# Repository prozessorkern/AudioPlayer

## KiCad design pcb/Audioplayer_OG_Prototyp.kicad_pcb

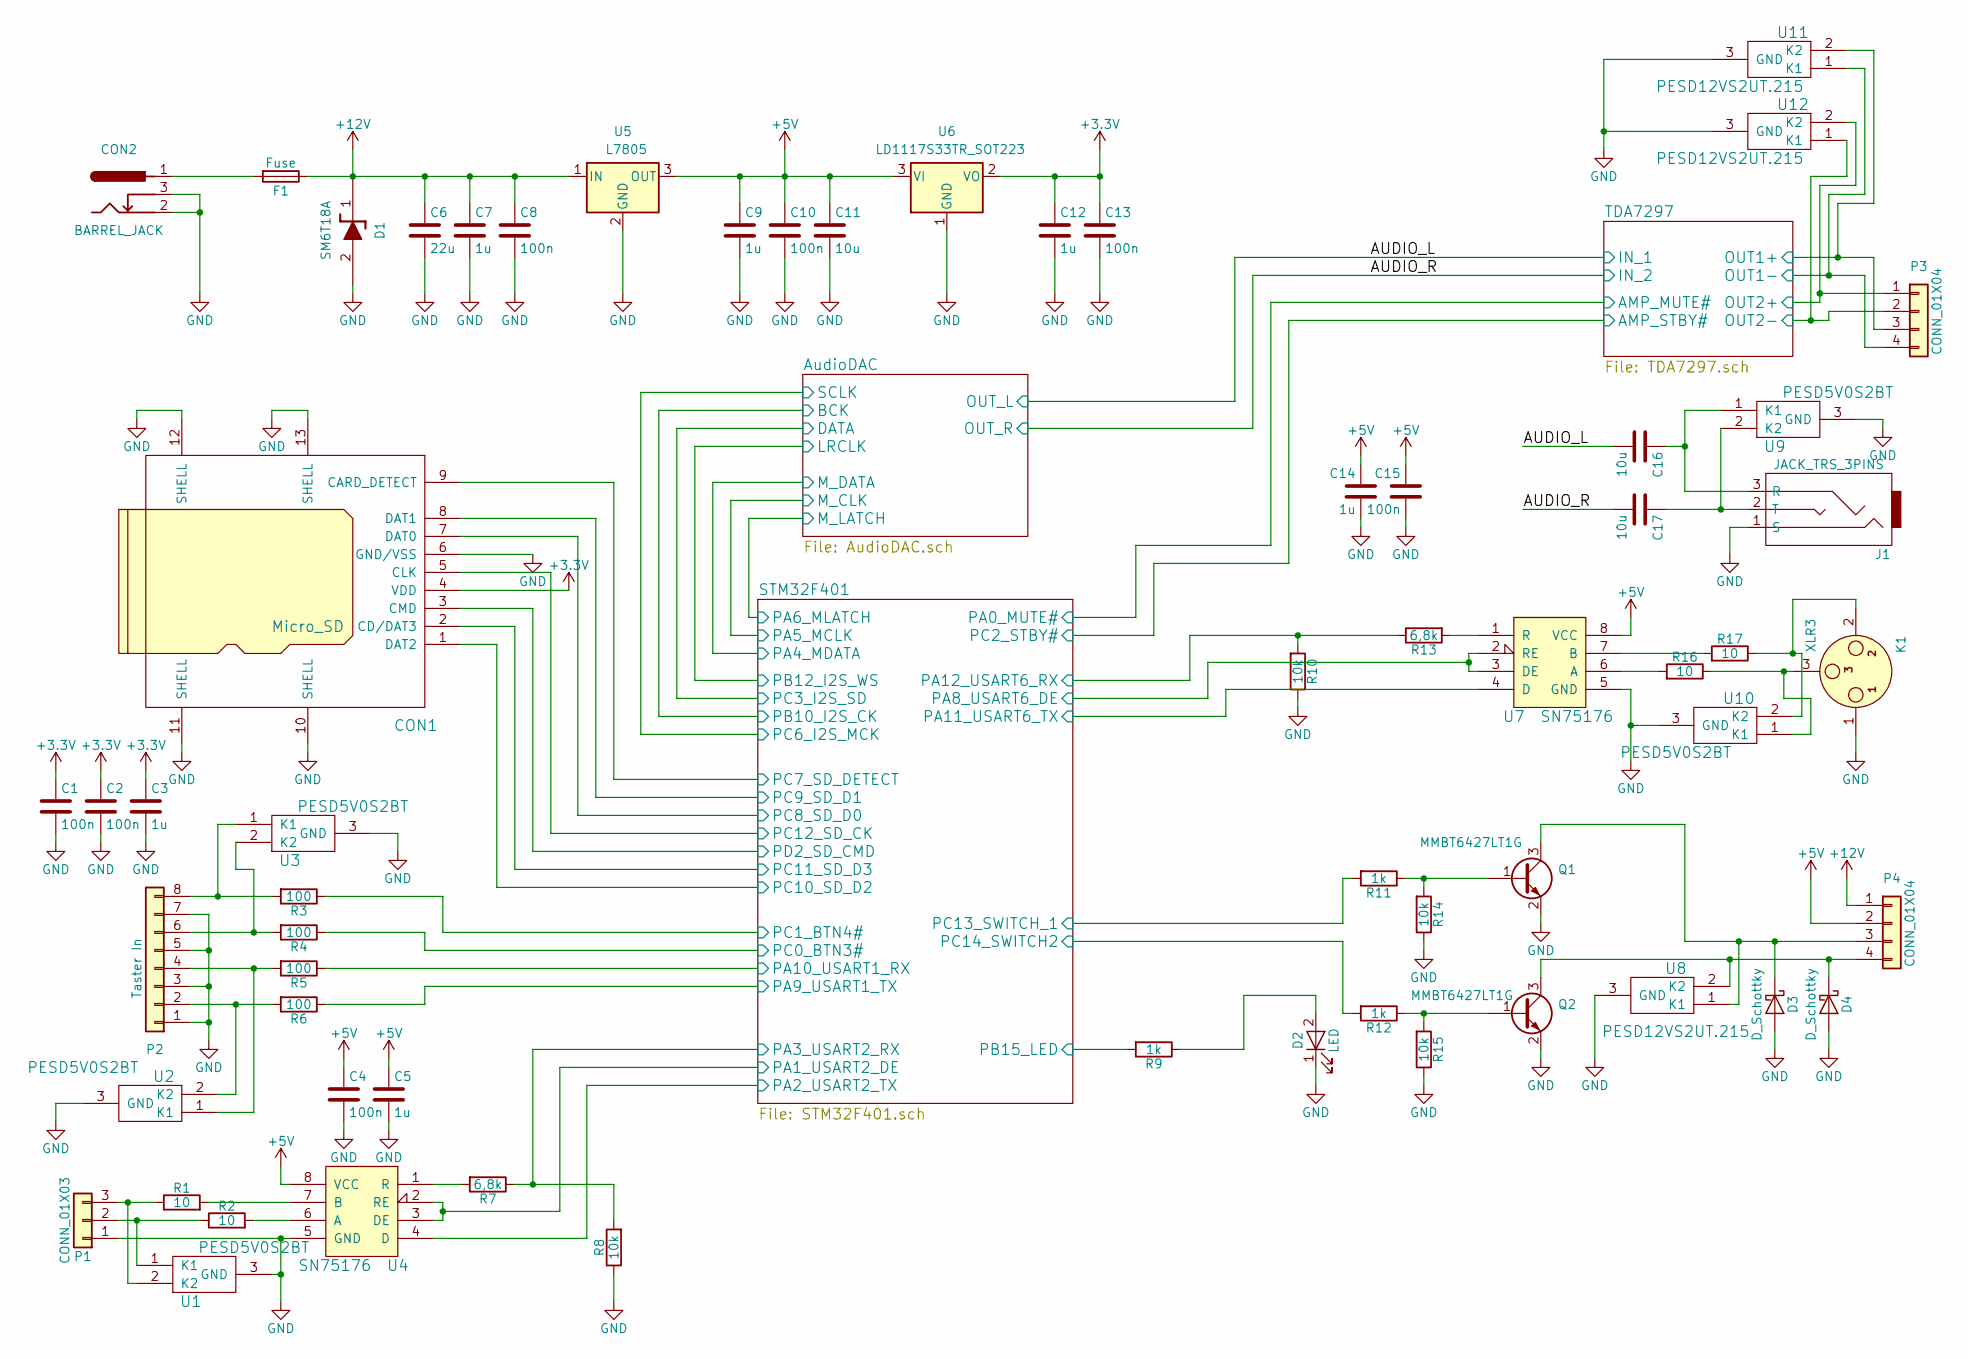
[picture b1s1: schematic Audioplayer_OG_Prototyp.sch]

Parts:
C1, C2, C4, C10, C13, C15: 100n; C_0603_HandSoldering
C3, C5, C9, C12, C14: 1u; C_0603_HandSoldering
C6: 22u; C_1210_HandSoldering
C7: 1u; C_0805_HandSoldering
C8: 100n; C_0805_HandSoldering
C11, C16, C17: 10u; C_0805_HandSoldering
CON1: Micro_SD
CON2: BARREL_JACK; BARREL_JACK_CLIFF
D1: SM6T18A; D_SMB_Handsoldering
D2: LED; LED_D3.0mm
D3, D4: D_Schottky; D_MELF_Handsoldering
F1: Fuse; Fuseholder5x20_ProFUSE
J1: JACK_TRS_3PINS; LUM_1503-07_Klinke
K1: XLR3; NC3FAH1_XLR_F
P1: CONN_01X03; 3PIN_5,00
P2: Taster In; 8PIN_3,5
P3, P4: CONN_01X04; 4PIN_5,00
Q1, Q2: MMBT6427LT1G; SOT-23_Handsoldering
R1, R2, R16, R17: 10; R_0603_HandSoldering
R3, R4, R5, R6: 100; R_0603_HandSoldering
R7, R13: 6,8k; R_0603_HandSoldering
R8, R10, R14, R15: 10k; R_0603_HandSoldering
R9, R11, R12: 1k; R_0603_HandSoldering
U1, U2, U3, U9, U10: PESD5V0S2BT; SOT-23_Handsoldering
U4, U7: SN75176; SO-8
U5: L7805; TO-263-2
U6: LD1117S33TR_SOT223; SOT-223-3_TabPin2
U8, U11, U12: PESD12VS2UT.215; SOT-23_Handsoldering

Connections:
+5V: C4.1, C5.1, C9.1, C10.1, C11.1, C14.1, C15.1, P4.2, U4.8 (VCC), U5.3 (OUT), U6.3 (VI), U7.8 (VCC); also elsewhere on the board
+12V: C6.1, C7.1, C8.1, D1.1, F1.1, P4.1, U5.1 (IN); also elsewhere on the board
/AUDIO_L: C16.2; also elsewhere on the board
/AUDIO_R: C17.2; also elsewhere on the board
/STM32F401/PA1_USART2_DE: U4.2 (RE), U4.3 (DE); also elsewhere on the board
/STM32F401/PA2_USART2_TX: U4.4 (D); also elsewhere on the board
/STM32F401/PA3_USART2_RX: R7.1, R8.2; also elsewhere on the board
/STM32F401/PA8_USART6_DE: U7.2 (RE), U7.3 (DE); also elsewhere on the board
/STM32F401/PA9_USART1_TX: R6.1; also elsewhere on the board
/STM32F401/PA10_USART1_RX: R5.1; also elsewhere on the board
/STM32F401/PA11_USART6_TX: U7.4 (D); also elsewhere on the board
/STM32F401/PA12_USART6_RX: R10.2, R13.1; also elsewhere on the board
/STM32F401/PB15_LED: R9.2; also elsewhere on the board
/STM32F401/PC0_BTN3#: R4.1; also elsewhere on the board
/STM32F401/PC1_BTN4#: R3.1; also elsewhere on the board
/STM32F401/PC7_SD_DETECT: CON1.9 (CARD_DETECT); also elsewhere on the board
/STM32F401/PC8_SD_D0: CON1.7 (DAT0); also elsewhere on the board
/STM32F401/PC9_SD_D1: CON1.8 (DAT1); also elsewhere on the board
/STM32F401/PC10_SD_D2: CON1.1 (DAT2); also elsewhere on the board
/STM32F401/PC11_SD_D3: CON1.2 (CD/DAT3); also elsewhere on the board
/STM32F401/PC12_SD_CK: CON1.5 (CLK); also elsewhere on the board
/STM32F401/PC13_SWITCH_1: R11.2; also elsewhere on the board
/STM32F401/PC14_SWITCH2: R12.2; also elsewhere on the board
/STM32F401/PD2_SD_CMD: CON1.3 (CMD); also elsewhere on the board
/TDA7297/OUT1+: P3.3, U11.2 (K2); also elsewhere on the board
/TDA7297/OUT1-: P3.4, U11.1 (K1); also elsewhere on the board
/TDA7297/OUT2+: P3.1, U12.2 (K2); also elsewhere on the board
/TDA7297/OUT2-: P3.2, U12.1 (K1); also elsewhere on the board
GND: C1.2, C2.2, C3.2, C4.2, C5.2, C6.2, C7.2, C8.2, C9.2, C10.2, C11.2, C12.2, C13.2, C14.2, C15.2, CON1.6 (GND/VSS), CON1.10 (SHELL), CON1.11 (SHELL), CON1.12 (SHELL), CON1.13 (SHELL), CON2.2, CON2.3, D1.2, D2.1 (K), D3.2 (A), D4.2 (A), J1.1 (S), K1.1, P1.1, P2.1, P2.3, P2.5, P2.7, Q1.2 (E), Q2.2 (E), R8.1, R10.1, R14.1, R15.1, U1.3 (GND), U2.3 (GND), U3.3 (GND), U4.5 (GND), U5.2 (GND), U6.1 (GND), U7.5 (GND), U8.3 (GND), U9.3 (GND), U10.3 (GND), U11.3 (GND), U12.3 (GND); also elsewhere on the board
unnamed: C16.1, J1.3 (R), U9.1 (K1)
unnamed: C17.1, J1.2 (T), U9.2 (K2)
unnamed: CON2.1, F1.2
unnamed: D2.2 (A), R9.1
unnamed: D3.1 (K), P4.3, Q1.3 (C), U8.1 (K1)
unnamed: D4.1 (K), P4.4, Q2.3 (C), U8.2 (K2)
unnamed: K1.2, R17.1, U10.2 (K2)
unnamed: K1.3, R16.1, U10.1 (K1)
unnamed: P1.2, R2.1, U1.1 (K1)
unnamed: P1.3, R1.1, U1.2 (K2)
unnamed: P2.2, R6.2, U2.2 (K2)
unnamed: P2.4, R5.2, U2.1 (K1)
unnamed: P2.6, R4.2, U3.2 (K2)
unnamed: P2.8, R3.2, U3.1 (K1)
unnamed: Q1.1 (B), R11.1, R14.2
unnamed: Q2.1 (B), R12.1, R15.2
unnamed: R1.2, U4.7 (B)
unnamed: R2.2, U4.6 (A)
unnamed: R7.2, U4.1 (R)
unnamed: R13.2, U7.1 (R)
unnamed: R16.2, U7.6 (A)
unnamed: R17.2, U7.7 (B)

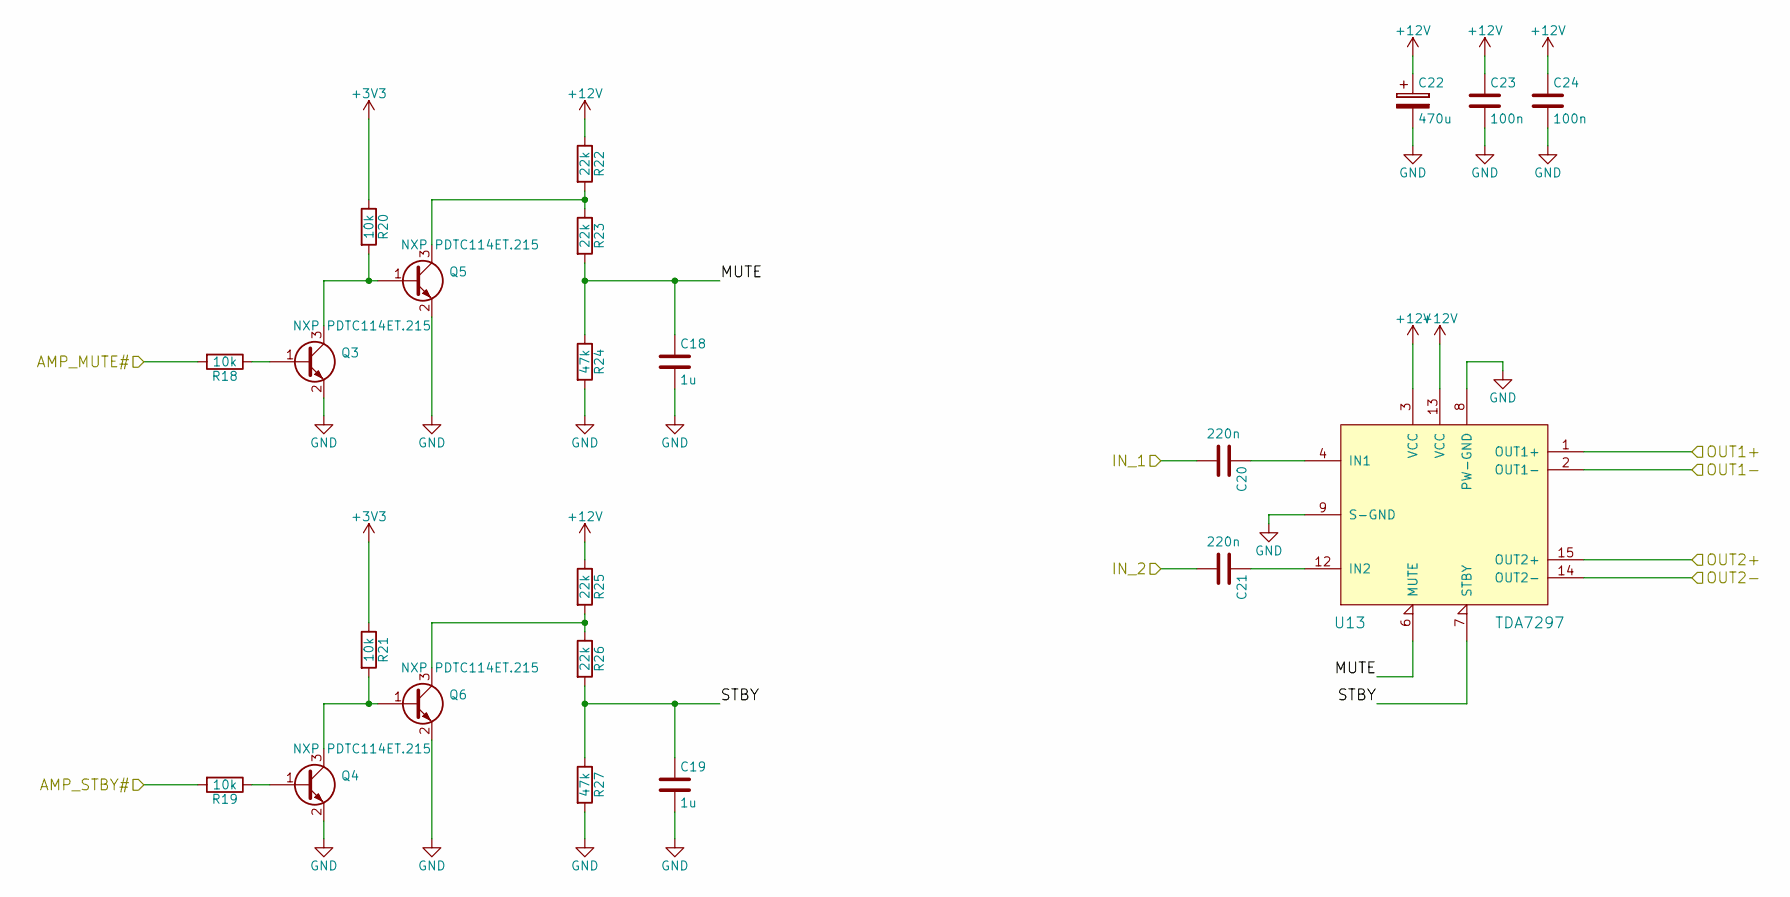
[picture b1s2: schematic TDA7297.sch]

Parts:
C18, C19: 1u; C_0603_HandSoldering
C20, C21: 220n; C_0603_HandSoldering
C22: 470u; CP_Radial_D10.0mm_P5.00mm
C23, C24: 100n; C_0805_HandSoldering
Q3, Q4, Q5, Q6: NXP PDTC114ET.215; SOT-23_Handsoldering
R18, R19, R20, R21: 10k; R_0603_HandSoldering
R22, R23, R25, R26: 22k; R_0603_HandSoldering
R24, R27: 47k; R_0603_HandSoldering
U13: TDA7297; TO-220-15_Vertical_StaggeredType1

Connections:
+12V: C22.1, C23.1, C24.1, R22.1, R25.1, U13.3 (VCC), U13.13 (VCC); also elsewhere on the board
/AUDIO_L: C20.2; also elsewhere on the board
/AUDIO_R: C21.2; also elsewhere on the board
/TDA7297/AMP_MUTE#: R18.2; also elsewhere on the board
/TDA7297/AMP_STBY#: R19.2; also elsewhere on the board
/TDA7297/MUTE: C18.1, R23.2, R24.1, U13.6 (MUTE)
/TDA7297/OUT1+: U13.1 (OUT1+); also elsewhere on the board
/TDA7297/OUT1-: U13.2 (OUT1-); also elsewhere on the board
/TDA7297/OUT2+: U13.15 (OUT2+); also elsewhere on the board
/TDA7297/OUT2-: U13.14 (OUT2-); also elsewhere on the board
/TDA7297/STBY: C19.1, R26.2, R27.1, U13.7 (STBY)
GND: C18.2, C19.2, C22.2, C23.2, C24.2, Q3.2 (E), Q4.2 (E), Q5.2 (E), Q6.2 (E), R24.2, R27.2, U13.8 (PW-GND), U13.9 (S-GND); also elsewhere on the board
unnamed: C20.1, U13.4 (IN1)
unnamed: C21.1, U13.12 (IN2)
unnamed: Q3.1 (B), R18.1
unnamed: Q3.3 (C), Q5.1 (B), R20.2
unnamed: Q4.1 (B), R19.1
unnamed: Q4.3 (C), Q6.1 (B), R21.2
unnamed: Q5.3 (C), R22.2, R23.1
unnamed: Q6.3 (C), R25.2, R26.1

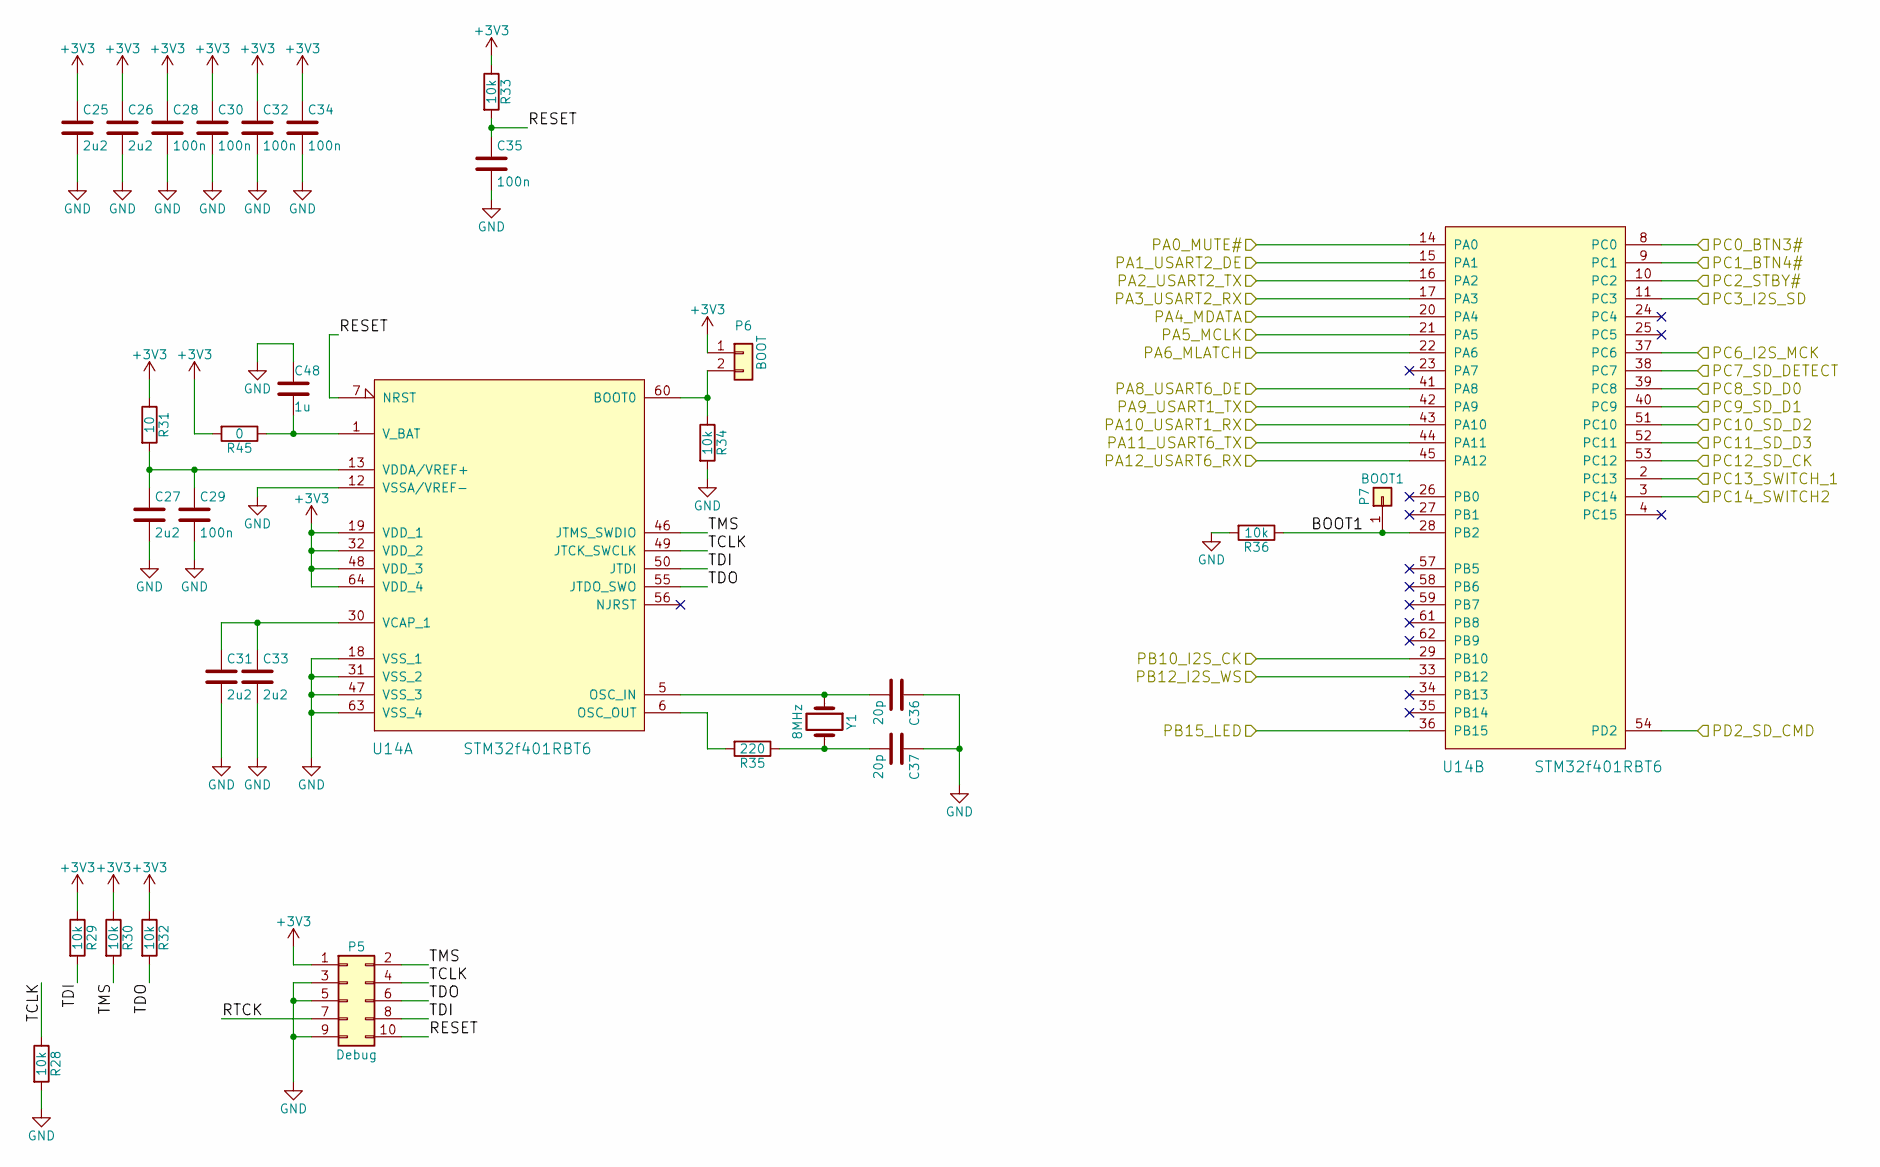
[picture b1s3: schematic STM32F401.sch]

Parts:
C25, C26, C27, C31, C33: 2u2; C_0603_HandSoldering
C28, C29, C30, C32, C34, C35: 100n; C_0603_HandSoldering
C36, C37: 20p; C_0603_HandSoldering
C48: 1u; C_0603_HandSoldering
P5: Debug; VASCH5x2
P6: BOOT; Pin_Header_Straight_1x02_Pitch2.54mm
P7: BOOT1; Pin_Header_Straight_1x01_Pitch2.54mm
R28, R29, R30, R32, R33, R34, R36: 10k; R_0603_HandSoldering
R31: 10; R_0603_HandSoldering
R35: 220; R_0603_HandSoldering
R45: 0; R_0603_HandSoldering
U14: STM32f401RBT6; LQFP-64_10x10mm_Pitch0.5mm
Y1: 8MHz; Crystal_HC49-U_Vertical

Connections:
/AudioDAC/BCK: U14.29 (PB10); also elsewhere on the board
/AudioDAC/DATA: U14.11 (PC3); also elsewhere on the board
/AudioDAC/LRCLK: U14.33 (PB12); also elsewhere on the board
/AudioDAC/M_CLK: U14.21 (PA5); also elsewhere on the board
/AudioDAC/M_DATA: U14.20 (PA4); also elsewhere on the board
/AudioDAC/M_LATCH: U14.22 (PA6); also elsewhere on the board
/STM32F401/BOOT1: P7.1, R36.1, U14.28 (PB2)
/STM32F401/PA1_USART2_DE: U14.15 (PA1); also elsewhere on the board
/STM32F401/PA2_USART2_TX: U14.16 (PA2); also elsewhere on the board
/STM32F401/PA3_USART2_RX: U14.17 (PA3); also elsewhere on the board
/STM32F401/PA8_USART6_DE: U14.41 (PA8); also elsewhere on the board
/STM32F401/PA9_USART1_TX: U14.42 (PA9); also elsewhere on the board
/STM32F401/PA10_USART1_RX: U14.43 (PA10); also elsewhere on the board
/STM32F401/PA11_USART6_TX: U14.44 (PA11); also elsewhere on the board
/STM32F401/PA12_USART6_RX: U14.45 (PA12); also elsewhere on the board
/STM32F401/PB15_LED: U14.36 (PB15); also elsewhere on the board
/STM32F401/PC0_BTN3#: U14.8 (PC0); also elsewhere on the board
/STM32F401/PC1_BTN4#: U14.9 (PC1); also elsewhere on the board
/STM32F401/PC6_I2S_MCK: U14.37 (PC6); also elsewhere on the board
/STM32F401/PC7_SD_DETECT: U14.38 (PC7); also elsewhere on the board
/STM32F401/PC8_SD_D0: U14.39 (PC8); also elsewhere on the board
/STM32F401/PC9_SD_D1: U14.40 (PC9); also elsewhere on the board
/STM32F401/PC10_SD_D2: U14.51 (PC10); also elsewhere on the board
/STM32F401/PC11_SD_D3: U14.52 (PC11); also elsewhere on the board
/STM32F401/PC12_SD_CK: U14.53 (PC12); also elsewhere on the board
/STM32F401/PC13_SWITCH_1: U14.2 (PC13); also elsewhere on the board
/STM32F401/PC14_SWITCH2: U14.3 (PC14); also elsewhere on the board
/STM32F401/PD2_SD_CMD: U14.54 (PD2); also elsewhere on the board
/STM32F401/RESET: C35.1, P5.10, R33.2, U14.7 (NRST)
/STM32F401/TCLK: P5.4, R28.1, U14.49 (JTCK_SWCLK)
/STM32F401/TDI: P5.8, R29.2, U14.50 (JTDI)
/STM32F401/TDO: P5.6, R32.2, U14.55 (JTDO_SWO)
/STM32F401/TMS: P5.2, R30.2, U14.46 (JTMS_SWDIO)
/TDA7297/AMP_MUTE#: U14.14 (PA0); also elsewhere on the board
/TDA7297/AMP_STBY#: U14.10 (PC2); also elsewhere on the board
GND: C25.2, C26.2, C27.2, C28.2, C29.2, C30.2, C31.2, C32.2, C33.2, C34.2, C35.2, C36.1, C37.1, C48.1, P5.3, P5.5, P5.9, R28.2, R34.2, R36.2, U14.12 (VSSA/VREF-), U14.18 (VSS_1), U14.31 (VSS_2), U14.47 (VSS_3), U14.63 (VSS_4); also elsewhere on the board
unnamed: C27.1, C29.1, R31.2, U14.13 (VDDA/VREF+)
unnamed: C31.1, C33.1, U14.30 (VCAP_1)
unnamed: C36.2, U14.5 (OSC_IN), Y1.1
unnamed: C37.2, R35.1, Y1.2
unnamed: C48.2, R45.1, U14.1 (V_BAT)
unnamed: P6.2, R34.1, U14.60 (BOOT0)
unnamed: R35.2, U14.6 (OSC_OUT)

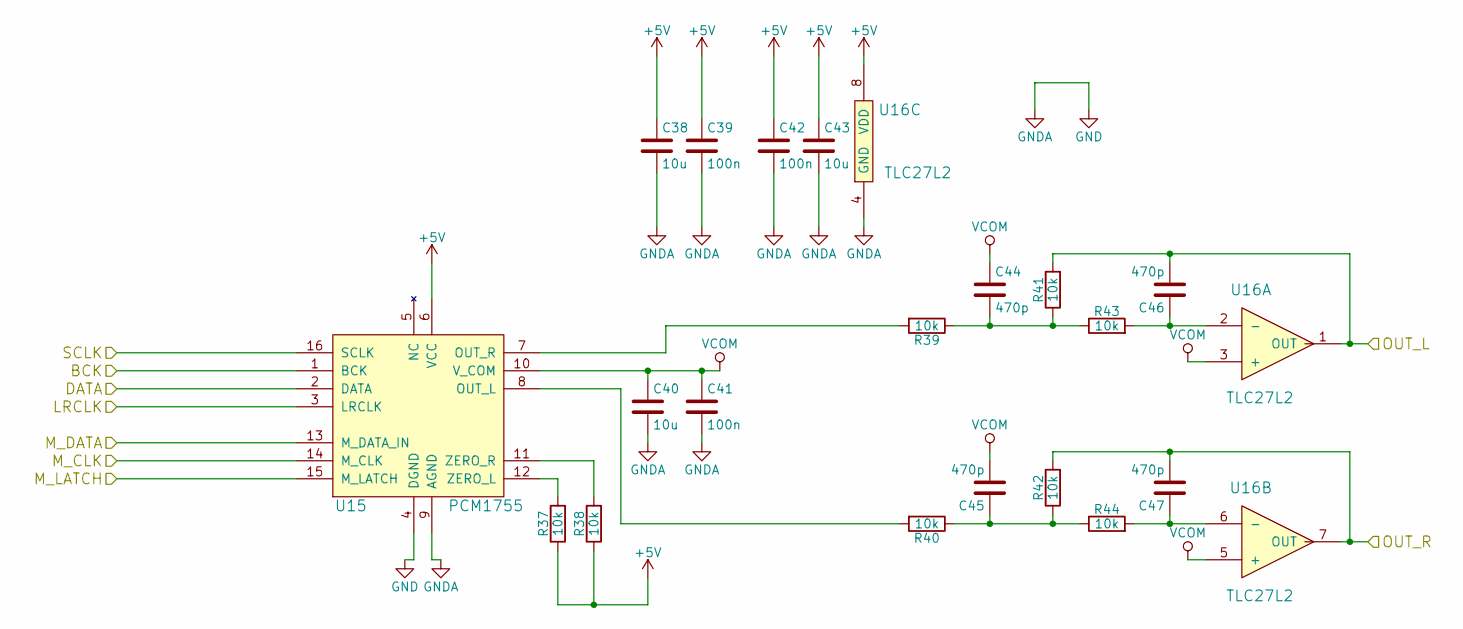
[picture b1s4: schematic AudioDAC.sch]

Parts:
C38, C40, C43: 10u; C_0805_HandSoldering
C39, C41, C42: 100n; C_0603_HandSoldering
C44, C45, C46, C47: 470p; C_0603_HandSoldering
R37, R38, R39, R40, R41, R42, R43, R44: 10k; R_0603_HandSoldering
U15: PCM1755; SSOP-16_3.9x4.9mm_Pitch0.635mm
U16: TLC27L2; SO-8

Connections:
+5V: C38.1, C39.1, C42.1, C43.1, R37.1, R38.1, U15.6 (VCC), U16.8 (VDD); also elsewhere on the board
/AUDIO_L: C46.2, R41.2, U16.1 (OUT); also elsewhere on the board
/AUDIO_R: C47.2, R42.2, U16.7 (OUT); also elsewhere on the board
/AudioDAC/BCK: U15.1 (BCK); also elsewhere on the board
/AudioDAC/DATA: U15.2 (DATA); also elsewhere on the board
/AudioDAC/LRCLK: U15.3 (LRCLK); also elsewhere on the board
/AudioDAC/M_CLK: U15.14 (M_CLK); also elsewhere on the board
/AudioDAC/M_DATA: U15.13 (M_DATA_IN); also elsewhere on the board
/AudioDAC/M_LATCH: U15.15 (M_LATCH); also elsewhere on the board
/STM32F401/PC6_I2S_MCK: U15.16 (SCLK); also elsewhere on the board
GND: C38.2, C39.2, C40.2, C41.2, C42.2, C43.2, U15.4 (DGND), U15.9 (AGND), U16.4 (GND); also elsewhere on the board
unnamed: C44.2, R39.1, R41.1, R43.1
unnamed: C45.1, R40.1, R42.1, R44.1
unnamed: C46.1, R43.2, U16.2 (-)
unnamed: C47.1, R44.2, U16.6 (-)
unnamed: R37.2, U15.12 (ZERO_L)
unnamed: R38.2, U15.11 (ZERO_R)
unnamed: R39.2, U15.7 (OUT_R)
unnamed: R40.2, U15.8 (OUT_L)
VCOM: C40.1, C41.1, C44.1, C45.2, U15.10 (V_COM), U16.3 (+), U16.5 (+)

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
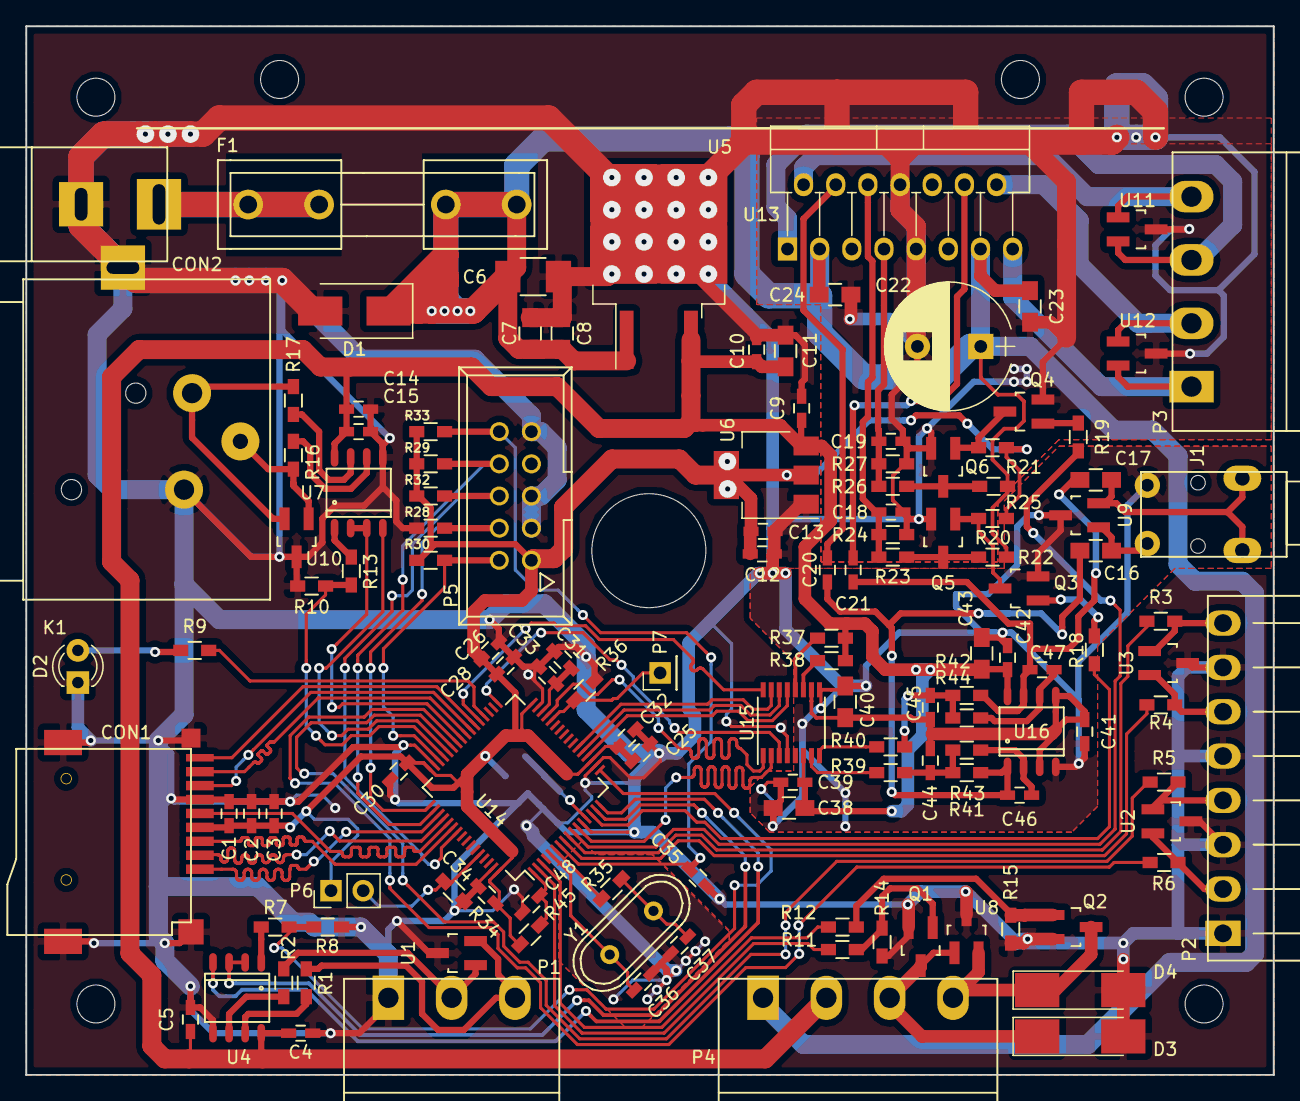
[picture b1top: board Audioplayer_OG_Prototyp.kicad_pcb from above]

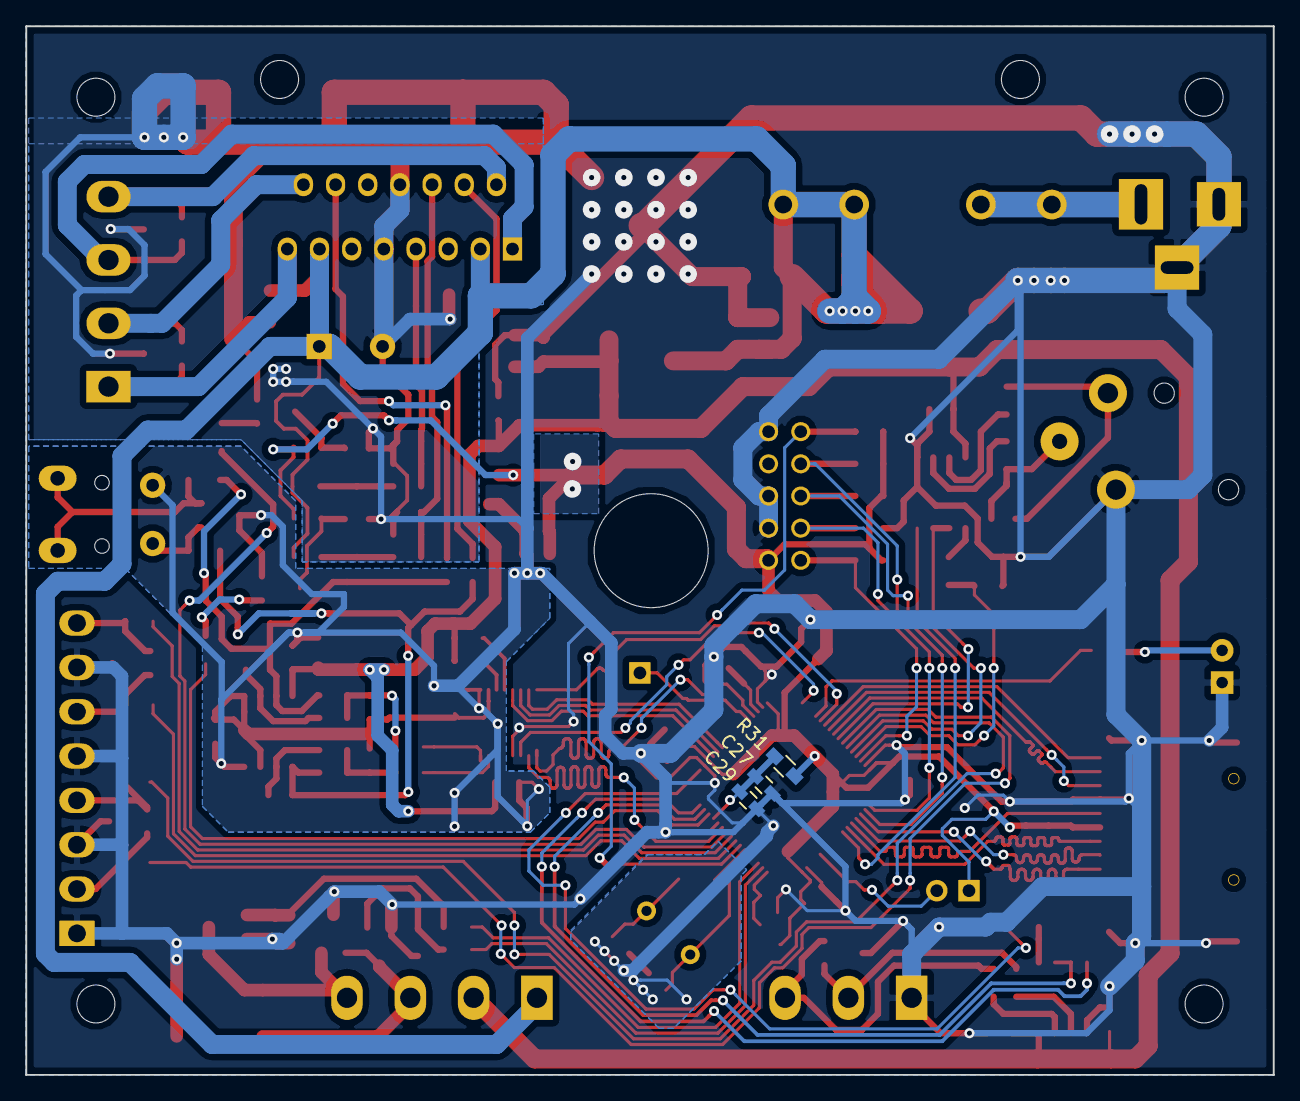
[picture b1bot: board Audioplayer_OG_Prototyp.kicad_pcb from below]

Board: 2 copper layers, 98.5 x 82.8 mm, 132 parts (3 on the bottom side), 93 nets.

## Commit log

2018-02-16 commit of the legacy work from another file management system...
    will be cleaned up afterwards
2018-02-16 cleaned up the project
    updated the KiCad Projects to run with the shared KiCad Libs
    changed to the new KiCad Lib Symbols and footprints
    simple Layout improvements
2018-02-16 Added GPL License File
2018-02-25 added a drawing of additional cutouts for the two extended connectors at the side of the audio player...
